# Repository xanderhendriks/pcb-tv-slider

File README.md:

# Starting KiCAD
Run the following command to start the used version of KiCAD:
```bash
docker compose up
```

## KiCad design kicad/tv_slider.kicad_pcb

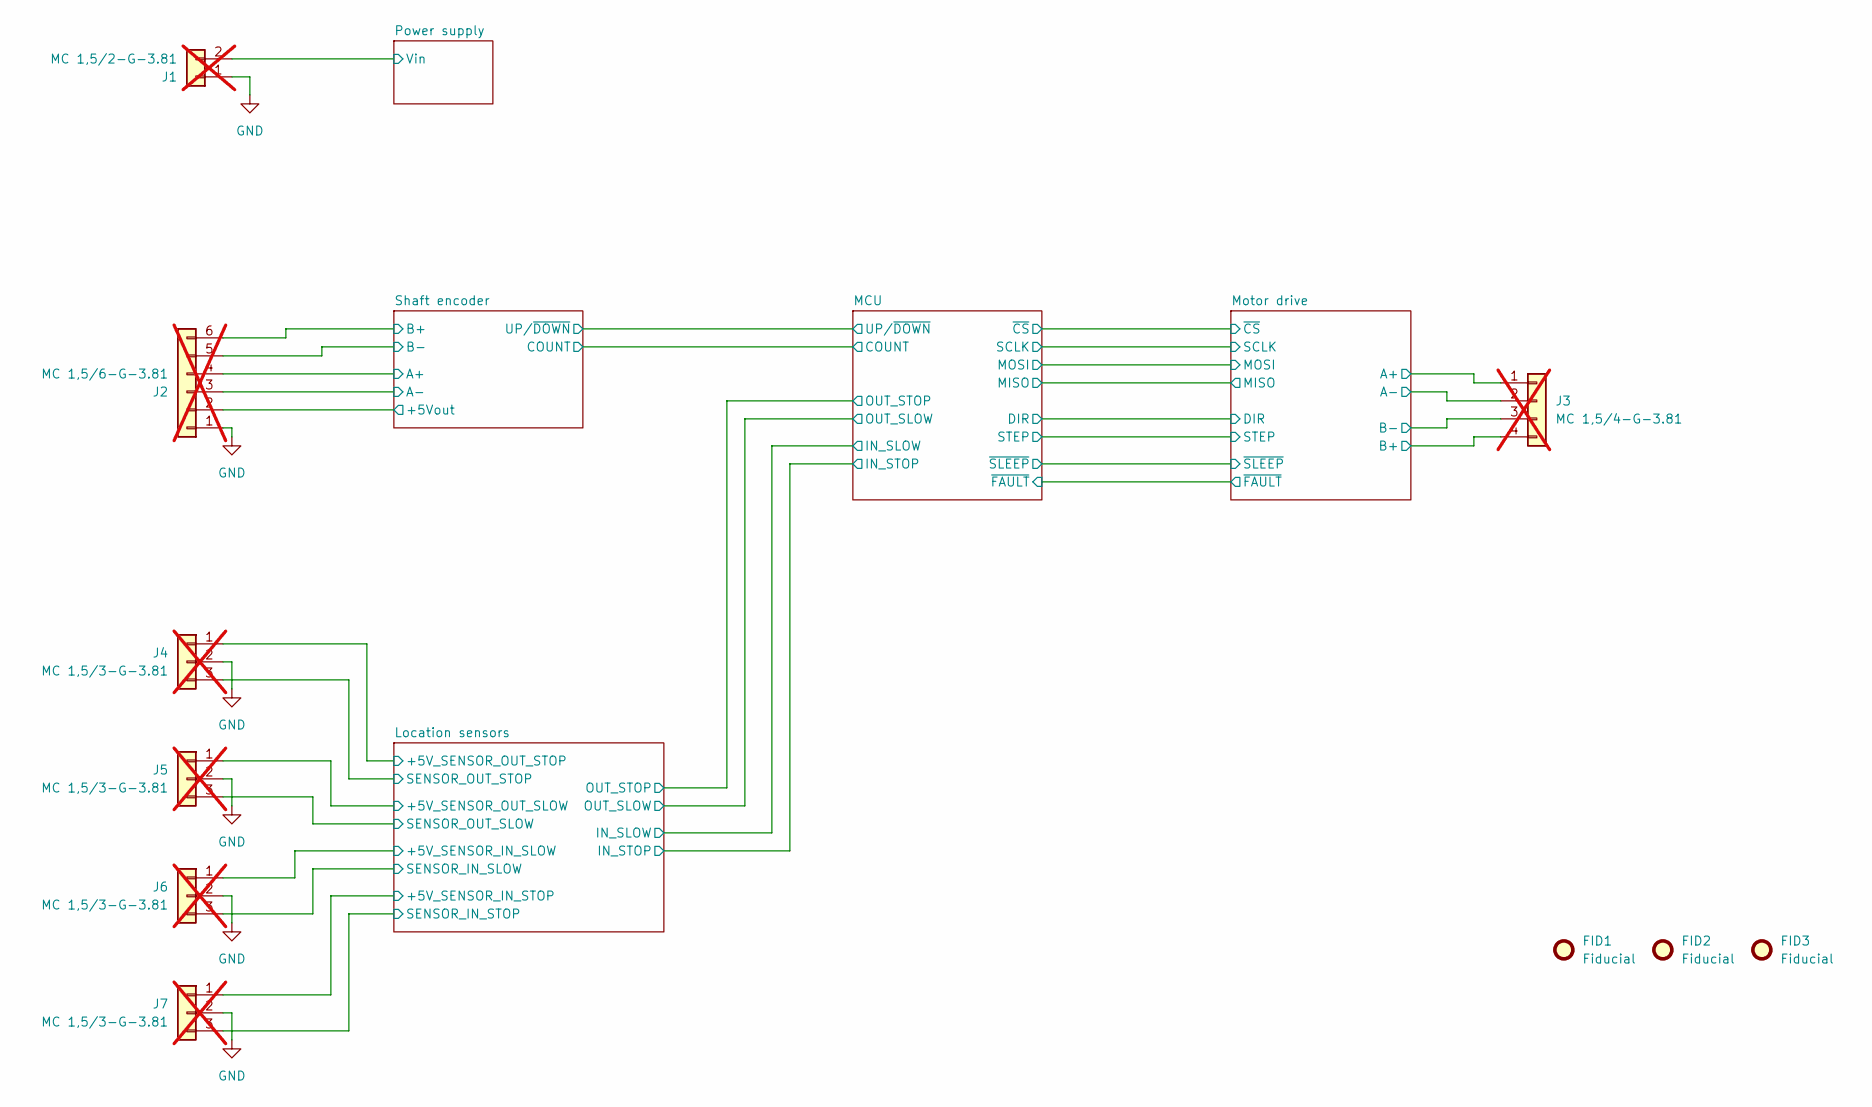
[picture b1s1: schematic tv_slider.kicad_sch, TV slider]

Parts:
FID1, FID2, FID3: Fiducial; Fiducial_1mm_Mask2mm
J1: MC 1,5/2-G-3.81; PhoenixContact_MC_1,5_2-G-3.81_1x02_P3.81mm_Horizontal; LCSC C480537; not fitted
J2: MC 1,5/6-G-3.81; PhoenixContact_MC_1,5_6-G-3.81_1x06_P3.81mm_Horizontal; LCSC C480580; not fitted
J3: MC 1,5/4-G-3.81; PhoenixContact_MC_1,5_4-G-3.81_1x04_P3.81mm_Horizontal; LCSC C480536; not fitted
J4, J5, J6, J7: MC 1,5/3-G-3.81; PhoenixContact_MC_1,5_3-G-3.81_1x03_P3.81mm_Horizontal; LCSC C480530; not fitted

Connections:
/Location sensors/+5V_SENSOR_IN_SLOW: J6.1; also elsewhere on the board
/Location sensors/+5V_SENSOR_IN_STOP: J7.1; also elsewhere on the board
/Location sensors/+5V_SENSOR_OUT_SLOW: J5.1; also elsewhere on the board
/Location sensors/+5V_SENSOR_OUT_STOP: J4.1; also elsewhere on the board
/Location sensors/SENSOR_IN_SLOW: J6.3; also elsewhere on the board
/Location sensors/SENSOR_IN_STOP: J7.3; also elsewhere on the board
/Location sensors/SENSOR_OUT_SLOW: J5.3; also elsewhere on the board
/Location sensors/SENSOR_OUT_STOP: J4.3; also elsewhere on the board
/Motor drive/A+: J3.1; also elsewhere on the board
/Motor drive/A-: J3.2; also elsewhere on the board
/Motor drive/B+: J3.4; also elsewhere on the board
/Motor drive/B-: J3.3; also elsewhere on the board
/Power supply/Vin: J1.2; also elsewhere on the board
/Shaft encoder/+5Vout: J2.2; also elsewhere on the board
/Shaft encoder/A+: J2.4; also elsewhere on the board
/Shaft encoder/A-: J2.3; also elsewhere on the board
/Shaft encoder/B+: J2.6; also elsewhere on the board
/Shaft encoder/B-: J2.5; also elsewhere on the board
GND: J1.1, J2.1, J4.2, J5.2, J6.2, J7.2; also elsewhere on the board

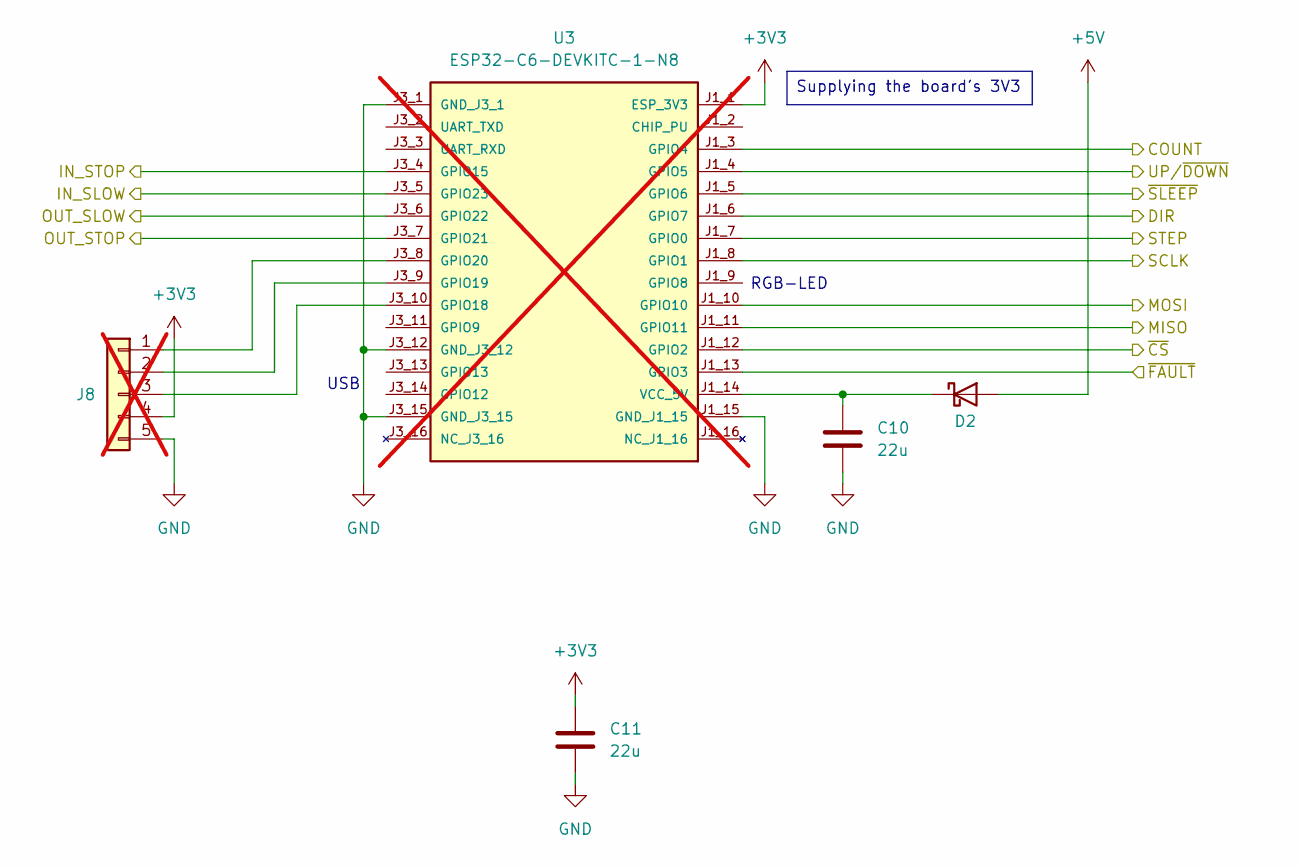
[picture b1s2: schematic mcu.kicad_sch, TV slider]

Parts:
C10, C11: 22u; C_1206_3216Metric; Voltage 25V; LCSC C12891
D2: 1N5819WS; D_SOD-323; Voltage 40V; LCSC C191023
J8: Conn_01x05; PinHeader_1x05_P2.54mm_Vertical; LCSC C6461551; not fitted
U3: ESP32-C6-DEVKITC-1-N8; MODULE_ESP32-C6-DEVKITC-1-N8; PARTREV 1.3; LCSC C20554022; not fitted

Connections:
+3V3: C11.1, J8.4, U3.J1_1 (ESP_3V3); also elsewhere on the board
+5V: D2.2 (A); also elsewhere on the board
/Location sensors/IN_SLOW: U3.J3_5 (GPIO23); also elsewhere on the board
/Location sensors/IN_STOP: U3.J3_4 (GPIO15); also elsewhere on the board
/Location sensors/OUT_SLOW: U3.J3_6 (GPIO22); also elsewhere on the board
/Location sensors/OUT_STOP: U3.J3_7 (GPIO21); also elsewhere on the board
/MCU/COUNT: U3.J1_3 (GPIO4); also elsewhere on the board
/MCU/DIR: U3.J1_6 (GPIO7); also elsewhere on the board
/MCU/MISO: U3.J1_11 (GPIO11); also elsewhere on the board
/MCU/MOSI: U3.J1_10 (GPIO10); also elsewhere on the board
/MCU/SCLK: U3.J1_8 (GPIO1); also elsewhere on the board
/MCU/STEP: U3.J1_7 (GPIO0); also elsewhere on the board
/MCU/UP/~DOWN: U3.J1_4 (GPIO5); also elsewhere on the board
/MCU/~CS: U3.J1_12 (GPIO2); also elsewhere on the board
/MCU/~FAULT: U3.J1_13 (GPIO3); also elsewhere on the board
/MCU/~SLEEP: U3.J1_5 (GPIO6); also elsewhere on the board
GND: C10.2, C11.2, J8.5, U3.J1_15 (GND_J1_15), U3.J3_1 (GND_J3_1), U3.J3_12 (GND_J3_12), U3.J3_15 (GND_J3_15); also elsewhere on the board
unnamed: C10.1, D2.1 (K), U3.J1_14 (VCC_5V)
unnamed: J8.1, U3.J3_8 (GPIO20)
unnamed: J8.2, U3.J3_9 (GPIO19)
unnamed: J8.3, U3.J3_10 (GPIO18)

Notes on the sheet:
USB
RGB-LED
Supplying the board's 3V3

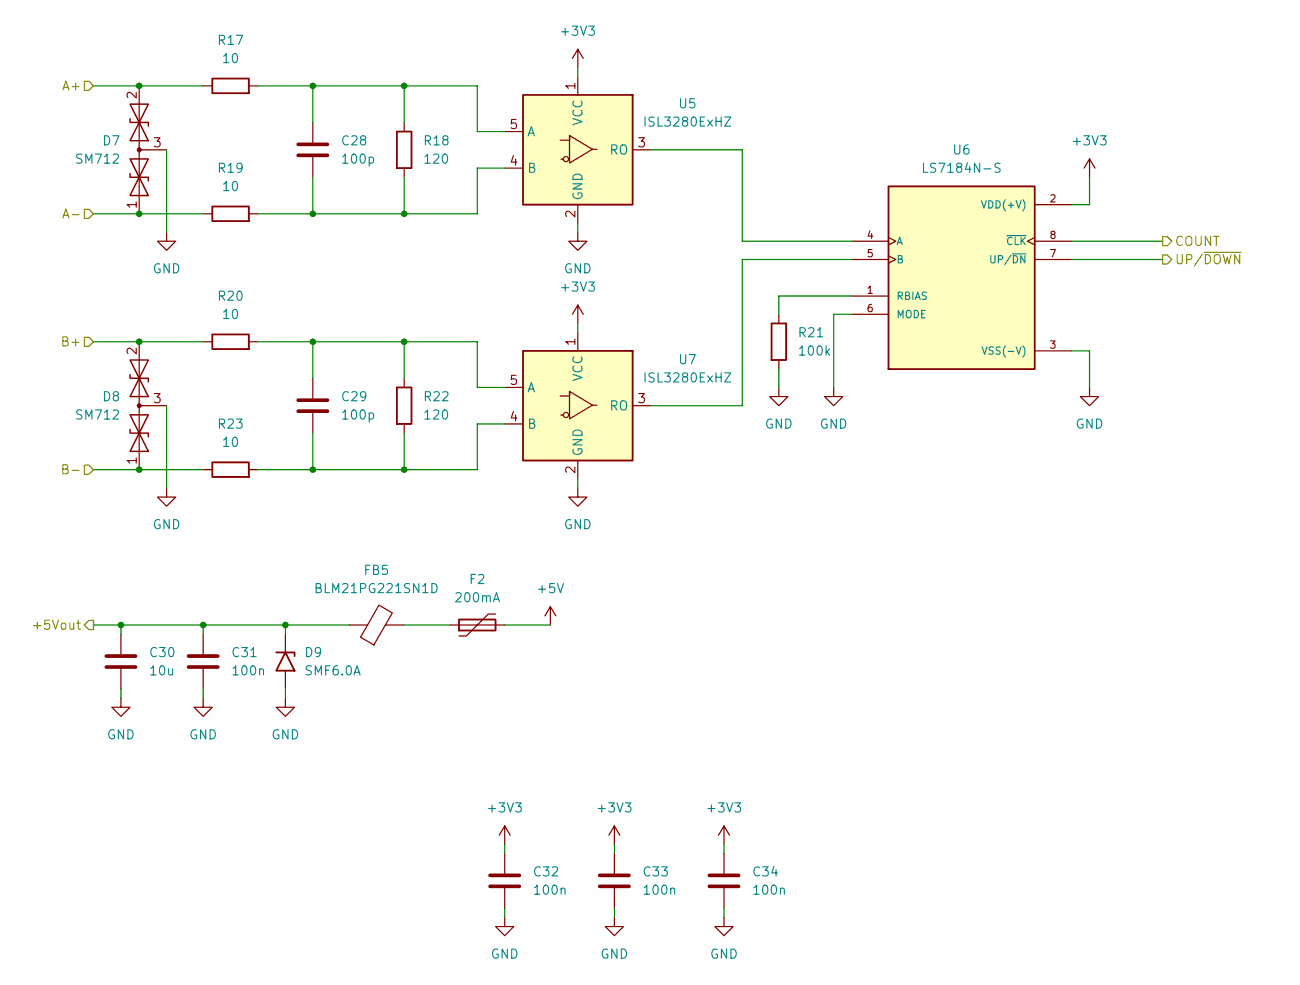
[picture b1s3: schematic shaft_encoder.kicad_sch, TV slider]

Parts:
C28, C29: 100p; C_0603_1608Metric; Voltage 50V; LCSC C14858
C30: 10u; C_0805_2012Metric; Voltage 50V; LCSC C440198
C31, C32, C33, C34: 100n; C_0603_1608Metric; Voltage 50V; LCSC C14663
D7, D8: SM712; SOT-23; LCSC C7420375
D9: SMF6.0A; D_SOD-123F; Voltage 10.3V; LCSC C19077499
F2: 200mA; Fuse_1206_3216Metric; LCSC C207035
FB5: BLM21PG221SN1D; L_0805_2012Metric; LCSC C1015
R17, R19, R20, R23: 10; R_0603_1608Metric; LCSC C22859
R18, R22: 120; R_0603_1608Metric; LCSC C22787
R21: 100k; R_0603_1608Metric; LCSC C25803
U5, U7: ISL3280ExHZ; SOT-23-5; LCSC C3227945
U6: LS7184N-S; SOIC127P600X175-8N; PARTREV June 2015; LCSC C3234980

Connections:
+3V3: C32.1, C33.1, C34.1, U5.1 (VCC), U6.2 (VDD(+V)), U7.1 (VCC); also elsewhere on the board
+5V: F2.2; also elsewhere on the board
/MCU/COUNT: U6.8 (~CLK); also elsewhere on the board
/MCU/UP/~DOWN: U6.7 (UP/~DN); also elsewhere on the board
/Shaft encoder/+5Vout: C30.1, C31.1, D9.1 (A1), FB5.1; also elsewhere on the board
/Shaft encoder/A+: D7.2 (A2), R17.1; also elsewhere on the board
/Shaft encoder/A-: D7.1 (A1), R19.1; also elsewhere on the board
/Shaft encoder/B+: D8.2 (A2), R20.1; also elsewhere on the board
/Shaft encoder/B-: D8.1 (A1), R23.1; also elsewhere on the board
GND: C30.2, C31.2, C32.2, C33.2, C34.2, D7.3 (common), D8.3 (common), D9.2 (A2), R21.2, U5.2 (GND), U6.3 (VSS(-V)), U6.6 (MODE), U7.2 (GND); also elsewhere on the board
unnamed: F2.1, FB5.2
unnamed: C28.1, R17.2, R18.1, U5.5 (A)
unnamed: C28.2, R18.2, R19.2, U5.4 (B)
unnamed: U5.3 (RO), U6.4 (A)
unnamed: U6.5 (B), U7.3 (RO)
unnamed: R21.1, U6.1 (RBIAS)
unnamed: C29.1, R20.2, R22.1, U7.5 (A)
unnamed: C29.2, R22.2, R23.2, U7.4 (B)

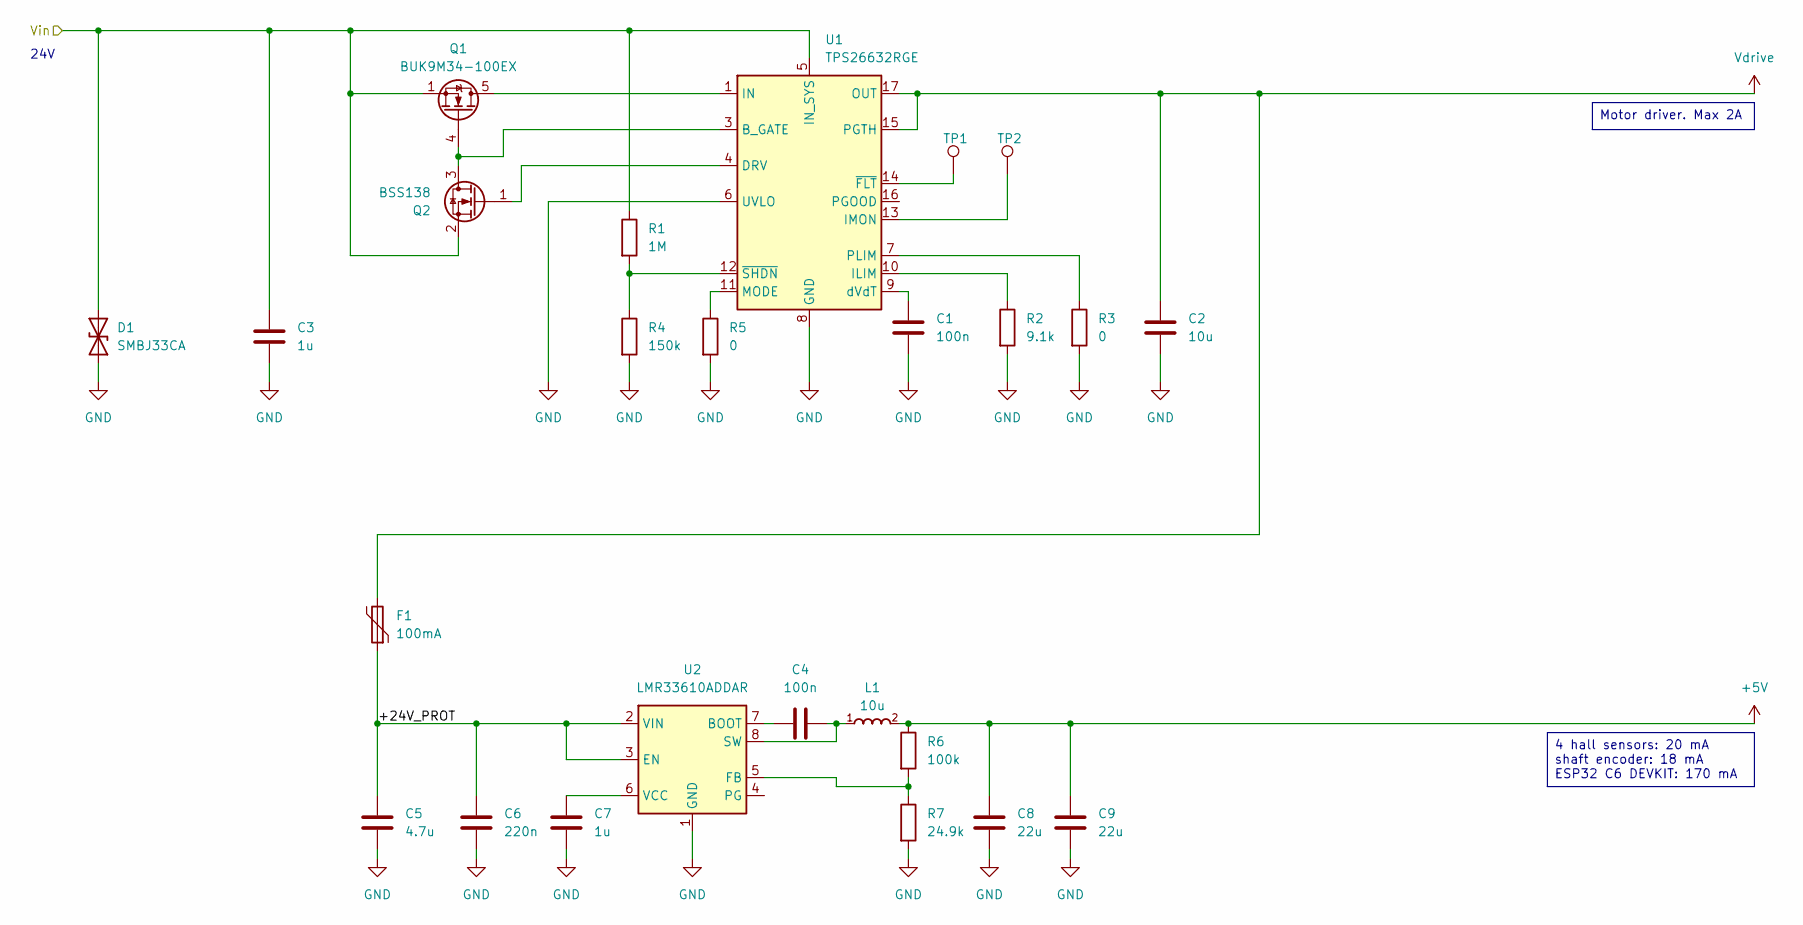
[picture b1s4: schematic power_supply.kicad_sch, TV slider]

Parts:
C1, C4: 100n; C_0603_1608Metric; Voltage 50V; LCSC C14663
C2: 10u; C_0805_2012Metric; Voltage 50V; LCSC C440198
C3, C7: 1u; C_0603_1608Metric; Voltage 50V; LCSC C15849
C5: 4.7u; C_0805_2012Metric; Voltage 50V; LCSC C162420
C6: 220n; C_0603_1608Metric; Voltage 50V; LCSC C64705
C8, C9: 22u; C_1206_3216Metric; Voltage 25V; LCSC C12891
D1: SMBJ33CA; D_SMB; Voltage 33V; LCSC C19077587
F1: 100mA; Fuse_1812_4532Metric; LCSC C12430
L1: 10u; IND_SRP4020TA-100M; LCSC C2847473
Q1: BUK9M34-100EX; LFPAK33; LCSC C550016
Q2: BSS138; SOT-23; LCSC C7420339
R1: 1M; R_0603_1608Metric; LCSC C22935
R2: 9.1k; R_0603_1608Metric; LCSC C23260
R3, R5: 0; R_0603_1608Metric; LCSC C21189
R4: 150k; R_0603_1608Metric; LCSC C22807
R6: 100k; R_0603_1608Metric; LCSC C25803
R7: 24.9k; R_0603_1608Metric; LCSC C25962
TP1: ~{FLT}; TestPoint_Pad_D1.0mm
TP2: IMON; TestPoint_Pad_D1.0mm
U1: TPS26632RGE; Texas_RGE0024H_VQFN-24-1EP_4x4mm_P0.5mm_EP2.7x2.7mm_Thermal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; LCSC C2862529
U2: LMR33610ADDAR; Texas_HSOP-8-1EP_3.9x4.9mm_P1.27mm_ThermalVias; LCSC C1852147

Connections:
+5V: C8.1, C9.1, L1.2, R6.1; also elsewhere on the board
/Power supply/+24V_PROT: C5.1, C6.1, F1.1, U2.2 (VIN), U2.3 (EN)
/Power supply/Vin: C3.1, D1.2 (A2), Q1.1 (S), Q1.2 (S), Q1.3 (S), Q2.2 (S), R1.1, U1.5 (IN_SYS); also elsewhere on the board
GND: C1.2, C2.2, C3.2, C5.2, C6.2, C7.2, C8.2, C9.2, D1.1 (A1), R2.2, R3.2, R4.2, R5.2, R7.2, U1.6 (UVLO), U1.8 (GND), U1.25 (GND), U2.1 (GND), U2.9 (GND); also elsewhere on the board
unnamed: Q1.5 (D), U1.1 (IN), U1.2 (IN)
unnamed: Q1.4 (G), Q2.3 (D), U1.3 (B_GATE)
unnamed: Q2.1 (G), U1.4 (DRV)
unnamed: R2.1, U1.10 (ILIM)
unnamed: TP2.1, U1.13 (IMON)
unnamed: R5.1, U1.11 (MODE)
unnamed: R3.1, U1.7 (PLIM)
unnamed: C1.1, U1.9 (dVdT)
unnamed: TP1.1, U1.14 (~FLT)
unnamed: R1.2, R4.1, U1.12 (~SHDN)
unnamed: C4.1, U2.7 (BOOT)
unnamed: R6.2, R7.1, U2.5 (FB)
unnamed: C4.2, L1.1, U2.8 (SW)
unnamed: C7.1, U2.6 (VCC)
Vdrive: C2.1, F1.2, U1.15 (PGTH), U1.17 (OUT), U1.18 (OUT); also elsewhere on the board

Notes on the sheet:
24V
4 hall sensors: 20 mA shaft encoder: 18 mA ESP32 C6 DEVKIT: 170 mA
Motor driver. Max 2A

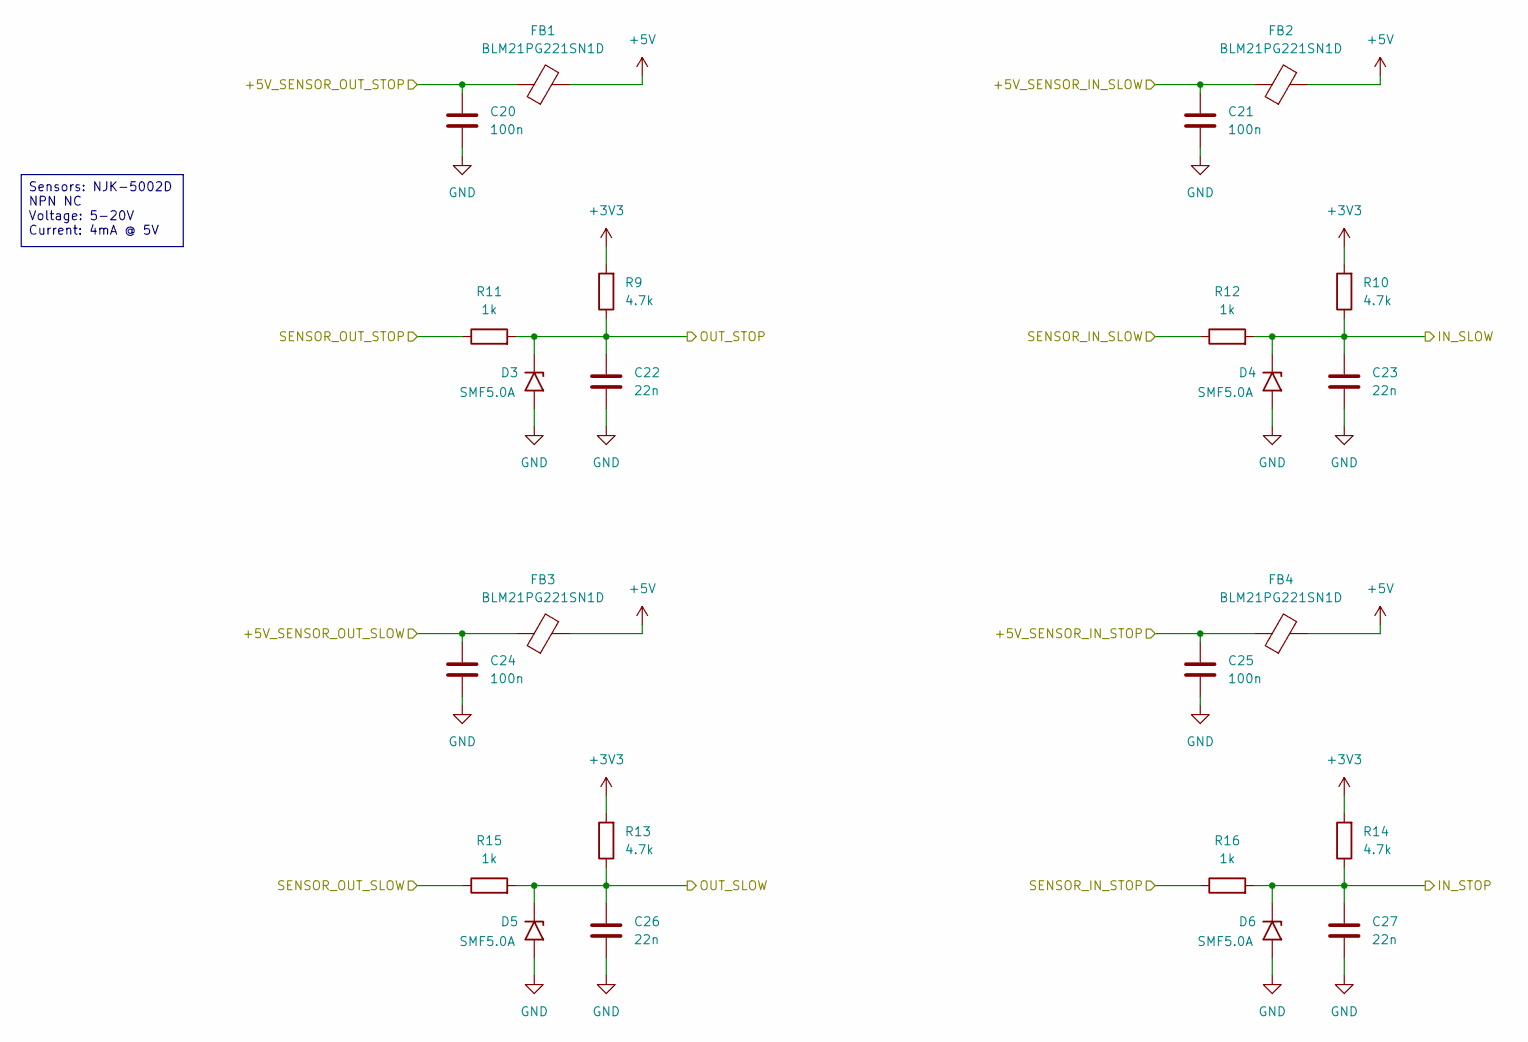
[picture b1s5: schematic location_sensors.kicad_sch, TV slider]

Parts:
C20, C21, C24, C25: 100n; C_0603_1608Metric; Voltage 50V; LCSC C14663
C22, C23, C26, C27: 22n; C_0603_1608Metric; Voltage 50V; LCSC C21122
D3, D4, D5, D6: SMF5.0A; D_SOD-123F; Voltage 9.2V; LCSC C19077497
FB1, FB2, FB3, FB4: BLM21PG221SN1D; L_0805_2012Metric; LCSC C1015
R9, R10, R13, R14: 4.7k; R_0603_1608Metric; LCSC C23162
R11, R12, R15, R16: 1k; R_0603_1608Metric; LCSC C21190

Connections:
+3V3: R9.2, R10.2, R13.2, R14.2; also elsewhere on the board
+5V: FB1.2, FB2.2, FB3.2, FB4.2; also elsewhere on the board
/Location sensors/+5V_SENSOR_IN_SLOW: C21.1, FB2.1; also elsewhere on the board
/Location sensors/+5V_SENSOR_IN_STOP: C25.1, FB4.1; also elsewhere on the board
/Location sensors/+5V_SENSOR_OUT_SLOW: C24.1, FB3.1; also elsewhere on the board
/Location sensors/+5V_SENSOR_OUT_STOP: C20.1, FB1.1; also elsewhere on the board
/Location sensors/IN_SLOW: C23.1, D4.1 (A1), R10.1, R12.2; also elsewhere on the board
/Location sensors/IN_STOP: C27.1, D6.1 (A1), R14.1, R16.2; also elsewhere on the board
/Location sensors/OUT_SLOW: C26.1, D5.1 (A1), R13.1, R15.2; also elsewhere on the board
/Location sensors/OUT_STOP: C22.1, D3.1 (A1), R9.1, R11.2; also elsewhere on the board
/Location sensors/SENSOR_IN_SLOW: R12.1; also elsewhere on the board
/Location sensors/SENSOR_IN_STOP: R16.1; also elsewhere on the board
/Location sensors/SENSOR_OUT_SLOW: R15.1; also elsewhere on the board
/Location sensors/SENSOR_OUT_STOP: R11.1; also elsewhere on the board
GND: C20.2, C21.2, C22.2, C23.2, C24.2, C25.2, C26.2, C27.2, D3.2 (A2), D4.2 (A2), D5.2 (A2), D6.2 (A2); also elsewhere on the board

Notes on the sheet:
Sensors: NJK-5002D NPN NC Voltage: 5-20V Current: 4mA @ 5V

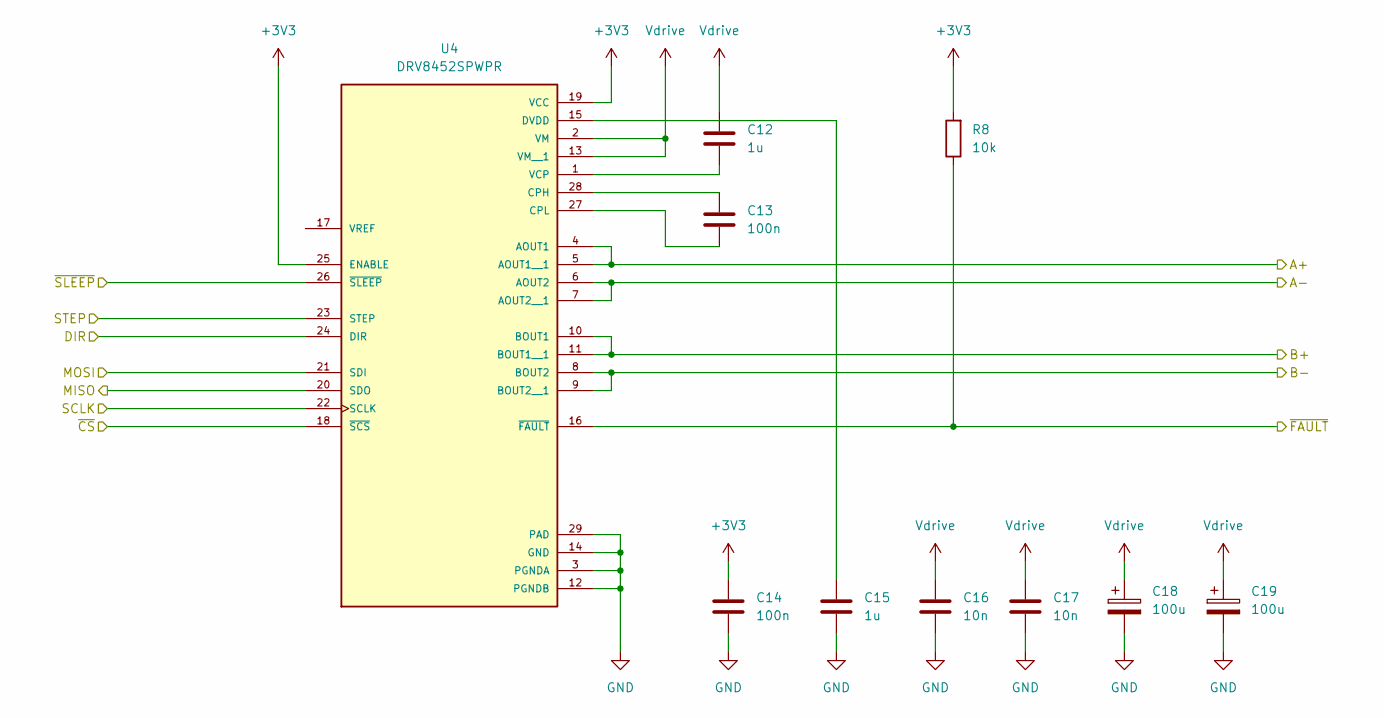
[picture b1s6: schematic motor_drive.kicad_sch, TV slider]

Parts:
C12, C15: 1u; C_0805_2012Metric; Voltage 50V; LCSC C28323
C13, C14: 100n; C_0603_1608Metric; Voltage 50V; LCSC C14663
C16, C17: 10n; C_0603_1608Metric; Voltage 50V; LCSC C57112
C18, C19: 100u; CP_Elec_8x11.9; Voltage 50V; LCSC C1517667
R8: 10k; R_0603_1608Metric; LCSC C25804
U4: DRV8452SPWPR; IC_DRV8452SPWPR; PARTREV B; LCSC C32469576

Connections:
+3V3: C14.1, R8.2, U4.19 (VCC), U4.25 (ENABLE); also elsewhere on the board
/MCU/DIR: U4.24 (DIR); also elsewhere on the board
/MCU/MISO: U4.20 (SDO); also elsewhere on the board
/MCU/MOSI: U4.21 (SDI); also elsewhere on the board
/MCU/SCLK: U4.22 (SCLK); also elsewhere on the board
/MCU/STEP: U4.23 (STEP); also elsewhere on the board
/MCU/~CS: U4.18 (~SCS); also elsewhere on the board
/MCU/~FAULT: R8.1, U4.16 (~FAULT); also elsewhere on the board
/MCU/~SLEEP: U4.26 (~SLEEP); also elsewhere on the board
/Motor drive/A+: U4.4 (AOUT1), U4.5 (AOUT1__1); also elsewhere on the board
/Motor drive/A-: U4.6 (AOUT2), U4.7 (AOUT2__1); also elsewhere on the board
/Motor drive/B+: U4.10 (BOUT1), U4.11 (BOUT1__1); also elsewhere on the board
/Motor drive/B-: U4.8 (BOUT2), U4.9 (BOUT2__1); also elsewhere on the board
GND: C14.2, C15.2, C16.2, C17.2, C18.2, C19.2, U4.3 (PGNDA), U4.12 (PGNDB), U4.14 (GND), U4.29 (PAD); also elsewhere on the board
unnamed: C13.1, U4.28 (CPH)
unnamed: C13.2, U4.27 (CPL)
unnamed: C15.1, U4.15 (DVDD)
unnamed: C12.2, U4.1 (VCP)
Vdrive: C12.1, C16.1, C17.1, C18.1, C19.1, U4.2 (VM), U4.13 (VM__1); also elsewhere on the board

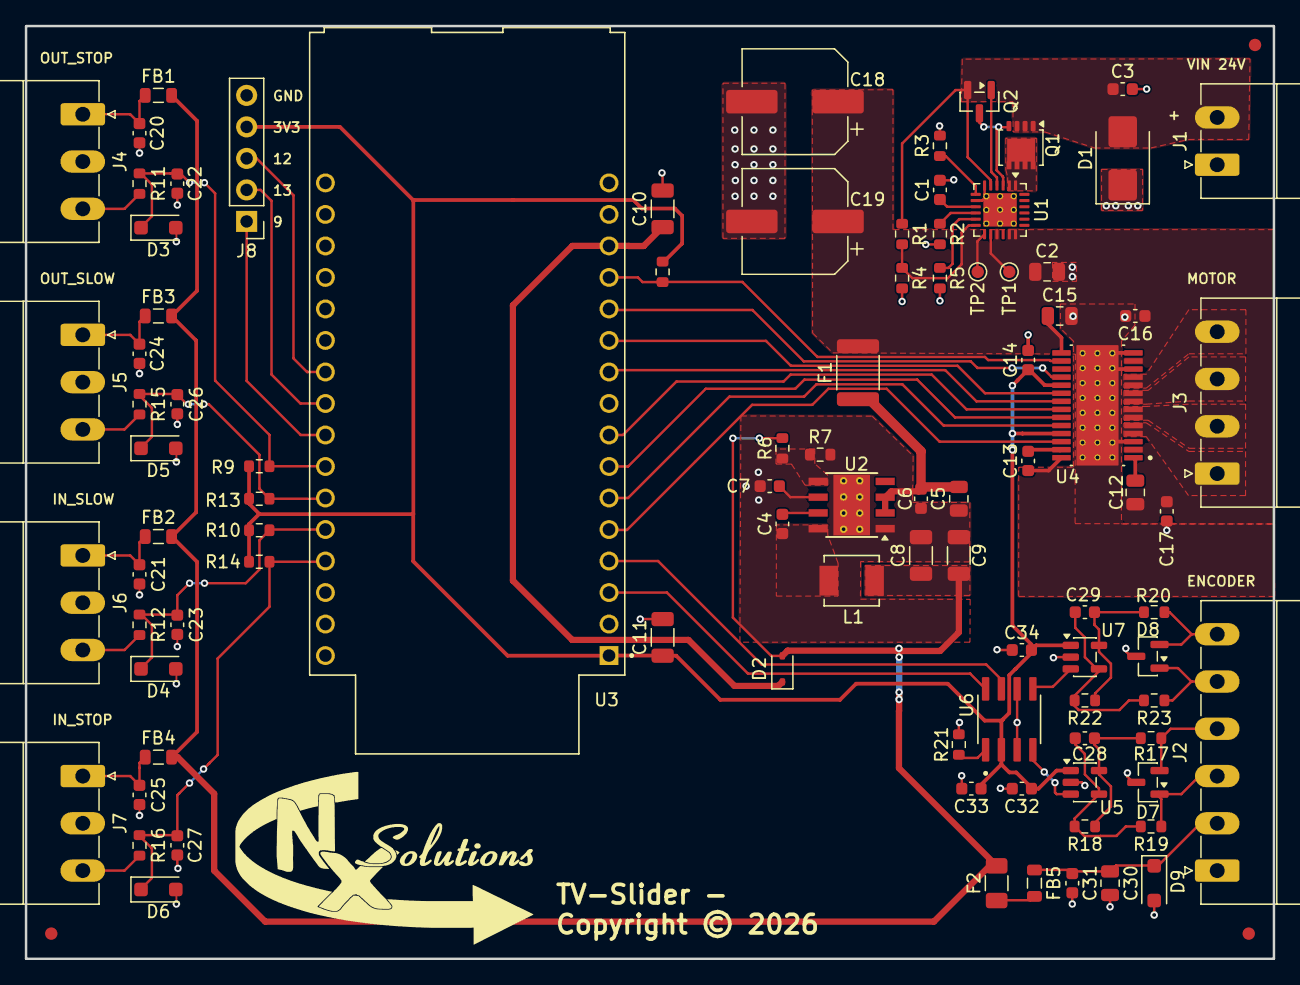
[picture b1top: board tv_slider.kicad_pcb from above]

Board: 2 copper layers, 100.6 x 75.2 mm, 96 parts (0 on the bottom side), 67 nets.

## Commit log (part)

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2025-09-25 Initial version with just the MCU DevKit
2025-10-04 top level schematic completed
2025-10-07 Completed the schematic. All components have Digikey part numbers and footprints. The power supply sheet still requires some work.
2025-10-13 Updated footprints and step models. Placed on PCB, but not yet positioned in final location.
2025-11-04 Added a compose file to start KiCAD from a docker and a README to explain how to use it.
2025-12-05 Updated all schematic pages except the power supply. Did the initial component placement.
2025-12-06 Removed /dev/dri, so it also works under wsl.
2025-12-14 Changed power supply chips as the 12V is no longer required.
2025-12-20 Finished the schematic and started the PCB.
2025-12-23 Completed the PCB design. Ready for final review.
2025-12-29 Reviewed the part numbers, footprints and pin numbers.
2025-12-30 Removed DNP for shaft encoder filtering
2025-12-30 DNP pushed through to PCB
2025-12-31 Re-annotated and added extra capacitors for the 5V and 3V3 DC-DC converters. Added testpoints to the electronic fuse.
2026-01-01 Fixed up or explained all DRC violations.
2026-01-02 Reviewed the ESP32-C6-DEVKIT GPIO's. Some of them have a dual function and are better left untouched.
2026-01-02 Supplying the ESP32-C6-DEVKIT with 5V and using its 3V3 output to supply the boards logic. Removed the 3V3 switch mode power supply on the board.
2026-01-02 Added extra copper for cooling the DRV8452SPWPR motor driver.
2026-01-02 Added some extra vias.
2026-01-02 Version 1.0 files as send to PCBWay
2026-01-04 Updated to use more of JCLPCB's basic components. Added extra field "FT Rotation Offset" to get the correct orientation for placement at JCLPCB.
2026-01-13 Fixed part number for DNP component.
2026-01-13 Fixed rotation for JLCPCB.

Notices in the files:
kicad/tv_slider.kicad_pcb:
Copyright © 2026
